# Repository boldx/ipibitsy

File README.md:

# IPIbitsy

[ēpˈbit-sē] \
Stuff to interface with an IBM 9347 9 track tape drive

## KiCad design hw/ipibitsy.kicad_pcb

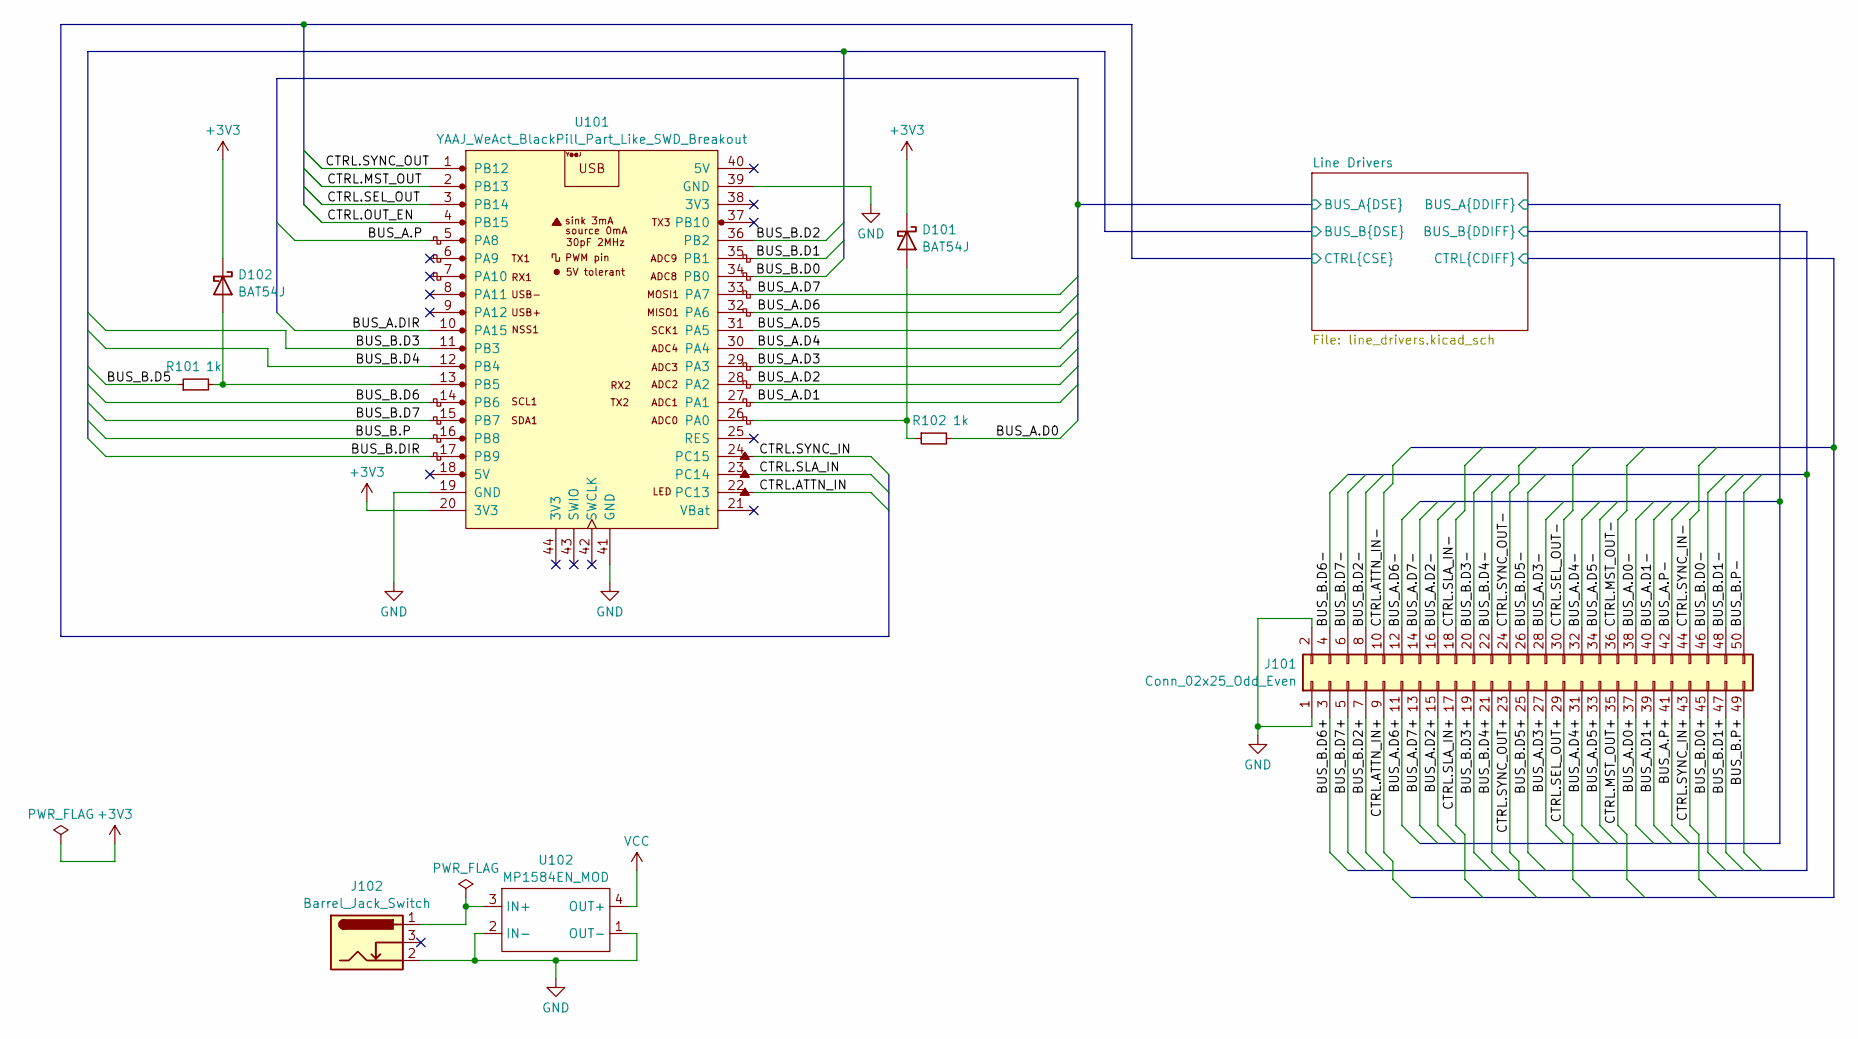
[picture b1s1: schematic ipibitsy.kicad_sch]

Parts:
D101, D102: BAT54J; D_SOD-323_HandSoldering
J101: Conn_02x25_Odd_Even; IDC-Header_2x25_P2.54mm_Vertical
J102: Barrel_Jack_Switch; BarrelJack_Horizontal
R101, R102: 1k; R_0603_1608Metric_Pad0.98x0.95mm_HandSolder
U101: YAAJ_WeAct_BlackPill_Part_Like_SWD_Breakout; YAAJ_WeAct_BlackPill_SWD_2
U102: MP1584EN_MOD

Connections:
+3V3: D101.1 (K), D102.1 (K), U101.20 (3V3)
/Line Drivers/BUS_A.D0: R102.2; also elsewhere on the board
/Line Drivers/BUS_A.D0+: J101.37; also elsewhere on the board
/Line Drivers/BUS_A.D0-: J101.38; also elsewhere on the board
/Line Drivers/BUS_A.D1: U101.27 (PA1); also elsewhere on the board
/Line Drivers/BUS_A.D1+: J101.39; also elsewhere on the board
/Line Drivers/BUS_A.D1-: J101.40; also elsewhere on the board
/Line Drivers/BUS_A.D2: U101.28 (PA2); also elsewhere on the board
/Line Drivers/BUS_A.D2+: J101.15; also elsewhere on the board
/Line Drivers/BUS_A.D2-: J101.16; also elsewhere on the board
/Line Drivers/BUS_A.D3: U101.29 (PA3); also elsewhere on the board
/Line Drivers/BUS_A.D3+: J101.27; also elsewhere on the board
/Line Drivers/BUS_A.D3-: J101.28; also elsewhere on the board
/Line Drivers/BUS_A.D4: U101.30 (PA4); also elsewhere on the board
/Line Drivers/BUS_A.D4+: J101.31; also elsewhere on the board
/Line Drivers/BUS_A.D4-: J101.32; also elsewhere on the board
/Line Drivers/BUS_A.D5: U101.31 (PA5); also elsewhere on the board
/Line Drivers/BUS_A.D5+: J101.33; also elsewhere on the board
/Line Drivers/BUS_A.D5-: J101.34; also elsewhere on the board
/Line Drivers/BUS_A.D6: U101.32 (PA6); also elsewhere on the board
/Line Drivers/BUS_A.D6+: J101.11; also elsewhere on the board
/Line Drivers/BUS_A.D6-: J101.12; also elsewhere on the board
/Line Drivers/BUS_A.D7: U101.33 (PA7); also elsewhere on the board
/Line Drivers/BUS_A.D7+: J101.13; also elsewhere on the board
/Line Drivers/BUS_A.D7-: J101.14; also elsewhere on the board
/Line Drivers/BUS_A.DIR: U101.10 (PA15); also elsewhere on the board
/Line Drivers/BUS_A.P: U101.5 (PA8); also elsewhere on the board
/Line Drivers/BUS_A.P+: J101.41; also elsewhere on the board
/Line Drivers/BUS_A.P-: J101.42; also elsewhere on the board
/Line Drivers/BUS_B.D0: U101.34 (PB0); also elsewhere on the board
/Line Drivers/BUS_B.D0+: J101.45; also elsewhere on the board
/Line Drivers/BUS_B.D0-: J101.46; also elsewhere on the board
/Line Drivers/BUS_B.D1: U101.35 (PB1); also elsewhere on the board
/Line Drivers/BUS_B.D1+: J101.47; also elsewhere on the board
/Line Drivers/BUS_B.D1-: J101.48; also elsewhere on the board
/Line Drivers/BUS_B.D2: U101.36 (PB2); also elsewhere on the board
/Line Drivers/BUS_B.D2+: J101.7; also elsewhere on the board
/Line Drivers/BUS_B.D2-: J101.8; also elsewhere on the board
/Line Drivers/BUS_B.D3: U101.11 (PB3); also elsewhere on the board
/Line Drivers/BUS_B.D3+: J101.19; also elsewhere on the board
/Line Drivers/BUS_B.D3-: J101.20; also elsewhere on the board
/Line Drivers/BUS_B.D4: U101.12 (PB4); also elsewhere on the board
/Line Drivers/BUS_B.D4+: J101.21; also elsewhere on the board
/Line Drivers/BUS_B.D4-: J101.22; also elsewhere on the board
/Line Drivers/BUS_B.D5: R101.1; also elsewhere on the board
/Line Drivers/BUS_B.D5+: J101.25; also elsewhere on the board
/Line Drivers/BUS_B.D5-: J101.26; also elsewhere on the board
/Line Drivers/BUS_B.D6: U101.14 (PB6); also elsewhere on the board
/Line Drivers/BUS_B.D6+: J101.3; also elsewhere on the board
/Line Drivers/BUS_B.D6-: J101.4; also elsewhere on the board
/Line Drivers/BUS_B.D7: U101.15 (PB7); also elsewhere on the board
/Line Drivers/BUS_B.D7+: J101.5; also elsewhere on the board
/Line Drivers/BUS_B.D7-: J101.6; also elsewhere on the board
/Line Drivers/BUS_B.DIR: U101.17 (PB9); also elsewhere on the board
/Line Drivers/BUS_B.P: U101.16 (PB8); also elsewhere on the board
/Line Drivers/BUS_B.P+: J101.49; also elsewhere on the board
/Line Drivers/BUS_B.P-: J101.50; also elsewhere on the board
/Line Drivers/CTRL.ATTN_IN: U101.22 (PC13); also elsewhere on the board
/Line Drivers/CTRL.ATTN_IN+: J101.9; also elsewhere on the board
/Line Drivers/CTRL.ATTN_IN-: J101.10; also elsewhere on the board
/Line Drivers/CTRL.MST_OUT: U101.2 (PB13); also elsewhere on the board
/Line Drivers/CTRL.MST_OUT+: J101.35; also elsewhere on the board
/Line Drivers/CTRL.MST_OUT-: J101.36; also elsewhere on the board
/Line Drivers/CTRL.OUT_EN: U101.4 (PB15); also elsewhere on the board
/Line Drivers/CTRL.SEL_OUT: U101.3 (PB14); also elsewhere on the board
/Line Drivers/CTRL.SEL_OUT+: J101.29; also elsewhere on the board
/Line Drivers/CTRL.SEL_OUT-: J101.30; also elsewhere on the board
/Line Drivers/CTRL.SLA_IN: U101.23 (PC14); also elsewhere on the board
/Line Drivers/CTRL.SLA_IN+: J101.17; also elsewhere on the board
/Line Drivers/CTRL.SLA_IN-: J101.18; also elsewhere on the board
/Line Drivers/CTRL.SYNC_IN: U101.24 (PC15); also elsewhere on the board
/Line Drivers/CTRL.SYNC_IN+: J101.43; also elsewhere on the board
/Line Drivers/CTRL.SYNC_IN-: J101.44; also elsewhere on the board
/Line Drivers/CTRL.SYNC_OUT: U101.1 (PB12); also elsewhere on the board
/Line Drivers/CTRL.SYNC_OUT+: J101.23; also elsewhere on the board
/Line Drivers/CTRL.SYNC_OUT-: J101.24; also elsewhere on the board
unnamed: D101.2 (A), R102.1, U101.26 (PA0)
unnamed: D102.2 (A), R101.2, U101.13 (PB5)
unnamed: J102.1, U102.3 (IN+)

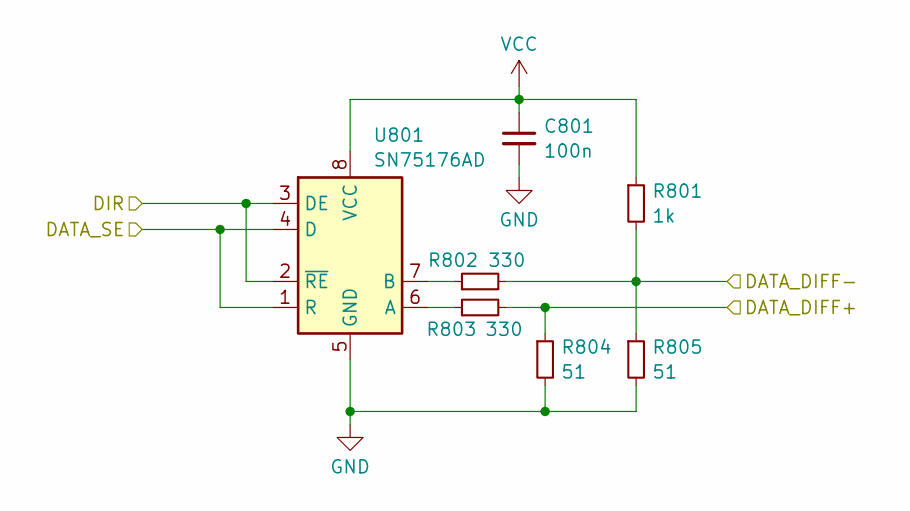
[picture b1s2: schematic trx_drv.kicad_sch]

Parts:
C801: 100n; C_0603_1608Metric_Pad1.08x0.95mm_HandSolder
R801: 1k; R_0603_1608Metric_Pad0.98x0.95mm_HandSolder
R802, R803: 330; R_0603_1608Metric_Pad0.98x0.95mm_HandSolder
R804, R805: 51; R_0603_1608Metric_Pad0.98x0.95mm_HandSolder
U801: SN75176AD; SOIC-8_3.9x4.9mm_P1.27mm

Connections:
/Line Drivers/BUS_A.D5: U801.1 (R), U801.4 (D); also elsewhere on the board
/Line Drivers/BUS_A.D5+: R803.2, R804.1; also elsewhere on the board
/Line Drivers/BUS_A.D5-: R801.2, R802.2, R805.1; also elsewhere on the board
/Line Drivers/BUS_A.DIR: U801.2 (~RE), U801.3 (DE); also elsewhere on the board
unnamed: R803.1, U801.6 (A)
unnamed: R802.1, U801.7 (B)

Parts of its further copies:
C301, C401, C501, C601, C701, C901, C1001, C1101, C1201, C1301, C1401, C1501, C1601, C1701, C1801, C1901, C2001, C2101, C2201, C2301, C2401, C2501, C2601: 100n; C_0603_1608Metric_Pad1.08x0.95mm_HandSolder
R301, R401, R501, R601, R701, R901, R1001, R1101, R1201, R1301, R1401, R1501, R1601, R1701, R1801, R1901, R2001, R2101, R2201, R2301, R2401, R2501, R2601: 1k; R_0603_1608Metric_Pad0.98x0.95mm_HandSolder
R302, R303, R402, R403, R502, R503, R602, R603, R702, R703, R902, R903, R1002, R1003, R1102, R1103, R1202, R1203, R1302, R1303, R1402, R1403, R1502, R1503, R1602, R1603, R1702, R1703, R1802, R1803, R1902, R1903, R2002, R2003, R2102, R2103, R2202, R2203, R2302, R2303, R2402, R2403, R2502, R2503, R2602, R2603: 330; R_0603_1608Metric_Pad0.98x0.95mm_HandSolder
R304, R305, R404, R405, R504, R505, R604, R605, R704, R705, R904, R905, R1004, R1005, R1104, R1105, R1204, R1205, R1304, R1305, R1404, R1405, R1504, R1505, R1604, R1605, R1704, R1705, R1804, R1805, R1904, R1905, R2004, R2005, R2104, R2105, R2204, R2205, R2304, R2305, R2404, R2405, R2504, R2505, R2604, R2605: 51; R_0603_1608Metric_Pad0.98x0.95mm_HandSolder
U301, U401, U501, U601, U701, U901, U1001, U1101, U1201, U1301, U1401, U1501, U1601, U1701, U1801, U1901, U2001, U2101, U2201, U2301, U2401, U2501, U2601: SN75176AD; SOIC-8_3.9x4.9mm_P1.27mm

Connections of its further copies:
/Line Drivers/BUS_A.D0: U301.1 (R), U301.4 (D); also elsewhere on the board
/Line Drivers/BUS_A.D0+: R303.2, R304.1; also elsewhere on the board
/Line Drivers/BUS_A.D0-: R301.2, R302.2, R305.1; also elsewhere on the board
/Line Drivers/BUS_A.D1: U401.1 (R), U401.4 (D); also elsewhere on the board
/Line Drivers/BUS_A.D1+: R403.2, R404.1; also elsewhere on the board
/Line Drivers/BUS_A.D1-: R401.2, R402.2, R405.1; also elsewhere on the board
/Line Drivers/BUS_A.D2: U501.1 (R), U501.4 (D); also elsewhere on the board
/Line Drivers/BUS_A.D2+: R503.2, R504.1; also elsewhere on the board
/Line Drivers/BUS_A.D2-: R501.2, R502.2, R505.1; also elsewhere on the board
/Line Drivers/BUS_A.D3: U601.1 (R), U601.4 (D); also elsewhere on the board
/Line Drivers/BUS_A.D3+: R603.2, R604.1; also elsewhere on the board
/Line Drivers/BUS_A.D3-: R601.2, R602.2, R605.1; also elsewhere on the board
/Line Drivers/BUS_A.D4: U701.1 (R), U701.4 (D); also elsewhere on the board
/Line Drivers/BUS_A.D4+: R703.2, R704.1; also elsewhere on the board
/Line Drivers/BUS_A.D4-: R701.2, R702.2, R705.1; also elsewhere on the board
/Line Drivers/BUS_A.D6: U901.1 (R), U901.4 (D); also elsewhere on the board
/Line Drivers/BUS_A.D6+: R903.2, R904.1; also elsewhere on the board
/Line Drivers/BUS_A.D6-: R901.2, R902.2, R905.1; also elsewhere on the board
/Line Drivers/BUS_A.D7: U1001.1 (R), U1001.4 (D); also elsewhere on the board
/Line Drivers/BUS_A.D7+: R1003.2, R1004.1; also elsewhere on the board
/Line Drivers/BUS_A.D7-: R1001.2, R1002.2, R1005.1; also elsewhere on the board
/Line Drivers/BUS_A.DIR: U301.2 (~RE), U301.3 (DE), U401.2 (~RE), U401.3 (DE), U501.2 (~RE), U501.3 (DE), U601.2 (~RE), U601.3 (DE), U701.2 (~RE), U701.3 (DE), U901.2 (~RE), U901.3 (DE), U1001.2 (~RE), U1001.3 (DE), U1101.2 (~RE), U1101.3 (DE); also elsewhere on the board
/Line Drivers/BUS_A.P: U1101.1 (R), U1101.4 (D); also elsewhere on the board
/Line Drivers/BUS_A.P+: R1103.2, R1104.1; also elsewhere on the board
/Line Drivers/BUS_A.P-: R1101.2, R1102.2, R1105.1; also elsewhere on the board
/Line Drivers/BUS_B.D0: U1201.1 (R), U1201.4 (D); also elsewhere on the board
/Line Drivers/BUS_B.D0+: R1203.2, R1204.1; also elsewhere on the board
/Line Drivers/BUS_B.D0-: R1201.2, R1202.2, R1205.1; also elsewhere on the board
/Line Drivers/BUS_B.D1: U1301.1 (R), U1301.4 (D); also elsewhere on the board
/Line Drivers/BUS_B.D1+: R1303.2, R1304.1; also elsewhere on the board
/Line Drivers/BUS_B.D1-: R1301.2, R1302.2, R1305.1; also elsewhere on the board
/Line Drivers/BUS_B.D2: U1401.1 (R), U1401.4 (D); also elsewhere on the board
/Line Drivers/BUS_B.D2+: R1403.2, R1404.1; also elsewhere on the board
/Line Drivers/BUS_B.D2-: R1401.2, R1402.2, R1405.1; also elsewhere on the board
/Line Drivers/BUS_B.D3: U1501.1 (R), U1501.4 (D); also elsewhere on the board
/Line Drivers/BUS_B.D3+: R1503.2, R1504.1; also elsewhere on the board
/Line Drivers/BUS_B.D3-: R1501.2, R1502.2, R1505.1; also elsewhere on the board
/Line Drivers/BUS_B.D4: U1601.1 (R), U1601.4 (D); also elsewhere on the board
/Line Drivers/BUS_B.D4+: R1603.2, R1604.1; also elsewhere on the board
/Line Drivers/BUS_B.D4-: R1601.2, R1602.2, R1605.1; also elsewhere on the board
/Line Drivers/BUS_B.D5: U1701.1 (R), U1701.4 (D); also elsewhere on the board
/Line Drivers/BUS_B.D5+: R1703.2, R1704.1; also elsewhere on the board
/Line Drivers/BUS_B.D5-: R1701.2, R1702.2, R1705.1; also elsewhere on the board
/Line Drivers/BUS_B.D6: U1801.1 (R), U1801.4 (D); also elsewhere on the board
/Line Drivers/BUS_B.D6+: R1803.2, R1804.1; also elsewhere on the board
/Line Drivers/BUS_B.D6-: R1801.2, R1802.2, R1805.1; also elsewhere on the board
/Line Drivers/BUS_B.D7: U1901.1 (R), U1901.4 (D); also elsewhere on the board
/Line Drivers/BUS_B.D7+: R1903.2, R1904.1; also elsewhere on the board
/Line Drivers/BUS_B.D7-: R1901.2, R1902.2, R1905.1; also elsewhere on the board
/Line Drivers/BUS_B.DIR: U1201.2 (~RE), U1201.3 (DE), U1301.2 (~RE), U1301.3 (DE), U1401.2 (~RE), U1401.3 (DE), U1501.2 (~RE), U1501.3 (DE), U1601.2 (~RE), U1601.3 (DE), U1701.2 (~RE), U1701.3 (DE), U1801.2 (~RE), U1801.3 (DE), U1901.2 (~RE), U1901.3 (DE), U2001.2 (~RE), U2001.3 (DE); also elsewhere on the board
/Line Drivers/BUS_B.P: U2001.1 (R), U2001.4 (D); also elsewhere on the board
/Line Drivers/BUS_B.P+: R2003.2, R2004.1; also elsewhere on the board
/Line Drivers/BUS_B.P-: R2001.2, R2002.2, R2005.1; also elsewhere on the board
/Line Drivers/CTRL.ATTN_IN: U2301.1 (R); also elsewhere on the board
/Line Drivers/CTRL.ATTN_IN+: R2303.2, R2304.1; also elsewhere on the board
/Line Drivers/CTRL.ATTN_IN-: R2301.2, R2302.2, R2305.1; also elsewhere on the board
/Line Drivers/CTRL.MST_OUT: U2501.4 (D); also elsewhere on the board
/Line Drivers/CTRL.MST_OUT+: R2503.2, R2504.1; also elsewhere on the board
/Line Drivers/CTRL.MST_OUT-: R2501.2, R2502.2, R2505.1; also elsewhere on the board
/Line Drivers/CTRL.OUT_EN: U2401.3 (DE), U2501.3 (DE), U2601.3 (DE); also elsewhere on the board
/Line Drivers/CTRL.SEL_OUT: U2601.4 (D); also elsewhere on the board
/Line Drivers/CTRL.SEL_OUT+: R2603.2, R2604.1; also elsewhere on the board
/Line Drivers/CTRL.SEL_OUT-: R2601.2, R2602.2, R2605.1; also elsewhere on the board
/Line Drivers/CTRL.SLA_IN: U2201.1 (R); also elsewhere on the board
/Line Drivers/CTRL.SLA_IN+: R2203.2, R2204.1; also elsewhere on the board
/Line Drivers/CTRL.SLA_IN-: R2201.2, R2202.2, R2205.1; also elsewhere on the board
/Line Drivers/CTRL.SYNC_IN: U2101.1 (R); also elsewhere on the board
/Line Drivers/CTRL.SYNC_IN+: R2103.2, R2104.1; also elsewhere on the board
/Line Drivers/CTRL.SYNC_IN-: R2101.2, R2102.2, R2105.1; also elsewhere on the board
/Line Drivers/CTRL.SYNC_OUT: U2401.4 (D); also elsewhere on the board
/Line Drivers/CTRL.SYNC_OUT+: R2403.2, R2404.1; also elsewhere on the board
/Line Drivers/CTRL.SYNC_OUT-: R2401.2, R2402.2, R2405.1; also elsewhere on the board
unnamed: R303.1, U301.6 (A)
unnamed: R302.1, U301.7 (B)
unnamed: R403.1, U401.6 (A)
unnamed: R402.1, U401.7 (B)
unnamed: R503.1, U501.6 (A)
unnamed: R502.1, U501.7 (B)
unnamed: R603.1, U601.6 (A)
unnamed: R602.1, U601.7 (B)
unnamed: R703.1, U701.6 (A)
unnamed: R702.1, U701.7 (B)
unnamed: R903.1, U901.6 (A)
unnamed: R902.1, U901.7 (B)
unnamed: R1003.1, U1001.6 (A)
unnamed: R1002.1, U1001.7 (B)
unnamed: R1103.1, U1101.6 (A)
unnamed: R1102.1, U1101.7 (B)
unnamed: R1203.1, U1201.6 (A)
unnamed: R1202.1, U1201.7 (B)
unnamed: R1303.1, U1301.6 (A)
unnamed: R1302.1, U1301.7 (B)
unnamed: R1403.1, U1401.6 (A)
unnamed: R1402.1, U1401.7 (B)
unnamed: R1503.1, U1501.6 (A)
unnamed: R1502.1, U1501.7 (B)
unnamed: R1603.1, U1601.6 (A)
unnamed: R1602.1, U1601.7 (B)
unnamed: R1703.1, U1701.6 (A)
unnamed: R1702.1, U1701.7 (B)
unnamed: R1803.1, U1801.6 (A)
unnamed: R1802.1, U1801.7 (B)
unnamed: R1903.1, U1901.6 (A)
unnamed: R1902.1, U1901.7 (B)
unnamed: R2003.1, U2001.6 (A)
unnamed: R2002.1, U2001.7 (B)
unnamed: R2103.1, U2101.6 (A)
unnamed: R2102.1, U2101.7 (B)
unnamed: R2203.1, U2201.6 (A)
unnamed: R2202.1, U2201.7 (B)
unnamed: R2303.1, U2301.6 (A)
unnamed: R2302.1, U2301.7 (B)
unnamed: R2403.1, U2401.6 (A)
unnamed: R2402.1, U2401.7 (B)
unnamed: R2503.1, U2501.6 (A)
unnamed: R2502.1, U2501.7 (B)
unnamed: R2603.1, U2601.6 (A)
unnamed: R2602.1, U2601.7 (B)

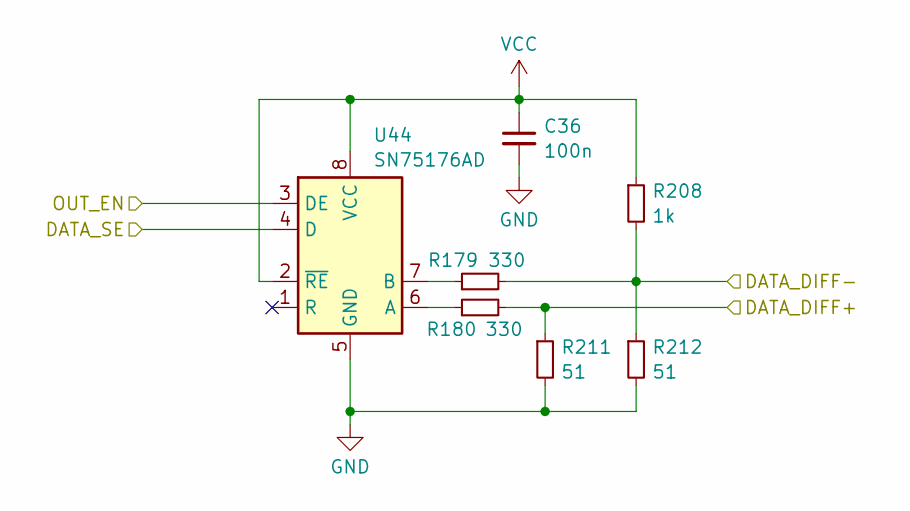
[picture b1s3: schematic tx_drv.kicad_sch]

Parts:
C36: 100n; C_0603_1608Metric_Pad1.08x0.95mm_HandSolder
R179, R180: 330; R_0603_1608Metric_Pad0.98x0.95mm_HandSolder
R208: 1k; R_0603_1608Metric_Pad0.98x0.95mm_HandSolder
R211, R212: 51; R_0603_1608Metric_Pad0.98x0.95mm_HandSolder
U44: SN75176AD; SOIC-8_3.9x4.9mm_P1.27mm

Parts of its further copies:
C2101, C2401, C2501, C2601: 100n; C_0603_1608Metric_Pad1.08x0.95mm_HandSolder
R2101, R2401, R2501, R2601: 1k; R_0603_1608Metric_Pad0.98x0.95mm_HandSolder
R2102, R2103, R2402, R2403, R2502, R2503, R2602, R2603: 330; R_0603_1608Metric_Pad0.98x0.95mm_HandSolder
R2104, R2105, R2404, R2405, R2504, R2505, R2604, R2605: 51; R_0603_1608Metric_Pad0.98x0.95mm_HandSolder
U2101, U2401, U2501, U2601: SN75176AD; SOIC-8_3.9x4.9mm_P1.27mm

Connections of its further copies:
/Line Drivers/CTRL.MST_OUT: U2501.4 (D); also elsewhere on the board
/Line Drivers/CTRL.MST_OUT+: R2503.2, R2504.1; also elsewhere on the board
/Line Drivers/CTRL.MST_OUT-: R2501.2, R2502.2, R2505.1; also elsewhere on the board
/Line Drivers/CTRL.OUT_EN: U2401.3 (DE), U2501.3 (DE), U2601.3 (DE); also elsewhere on the board
/Line Drivers/CTRL.SEL_OUT: U2601.4 (D); also elsewhere on the board
/Line Drivers/CTRL.SEL_OUT+: R2603.2, R2604.1; also elsewhere on the board
/Line Drivers/CTRL.SEL_OUT-: R2601.2, R2602.2, R2605.1; also elsewhere on the board
/Line Drivers/CTRL.SYNC_IN: U2101.1 (R); also elsewhere on the board
/Line Drivers/CTRL.SYNC_IN+: R2103.2, R2104.1; also elsewhere on the board
/Line Drivers/CTRL.SYNC_IN-: R2101.2, R2102.2, R2105.1; also elsewhere on the board
/Line Drivers/CTRL.SYNC_OUT: U2401.4 (D); also elsewhere on the board
/Line Drivers/CTRL.SYNC_OUT+: R2403.2, R2404.1; also elsewhere on the board
/Line Drivers/CTRL.SYNC_OUT-: R2401.2, R2402.2, R2405.1; also elsewhere on the board
unnamed: R2103.1, U2101.6 (A)
unnamed: R2102.1, U2101.7 (B)
unnamed: R2403.1, U2401.6 (A)
unnamed: R2402.1, U2401.7 (B)
unnamed: R2503.1, U2501.6 (A)
unnamed: R2502.1, U2501.7 (B)
unnamed: R2603.1, U2601.6 (A)
unnamed: R2602.1, U2601.7 (B)

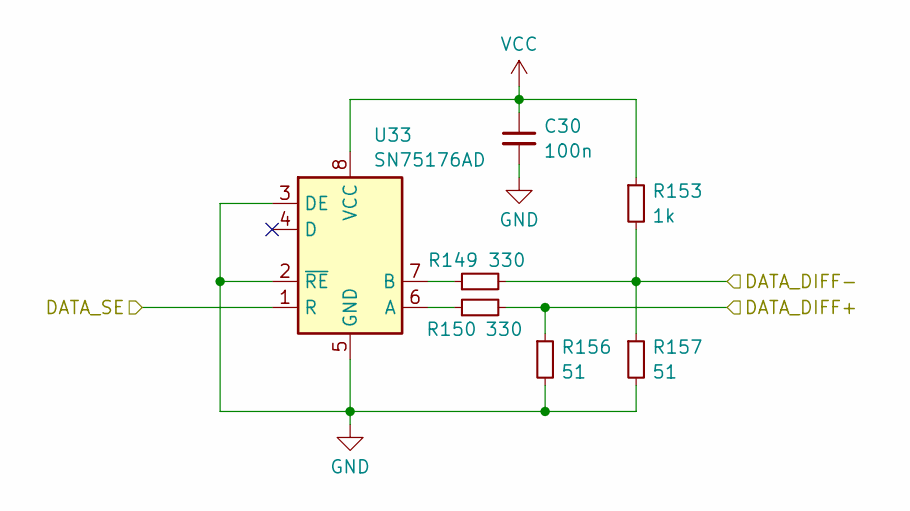
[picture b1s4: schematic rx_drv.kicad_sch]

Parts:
C30: 100n; C_0603_1608Metric_Pad1.08x0.95mm_HandSolder
R149, R150: 330; R_0603_1608Metric_Pad0.98x0.95mm_HandSolder
R153: 1k; R_0603_1608Metric_Pad0.98x0.95mm_HandSolder
R156, R157: 51; R_0603_1608Metric_Pad0.98x0.95mm_HandSolder
U33: SN75176AD; SOIC-8_3.9x4.9mm_P1.27mm

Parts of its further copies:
C2101, C2201, C2301: 100n; C_0603_1608Metric_Pad1.08x0.95mm_HandSolder
R2101, R2201, R2301: 1k; R_0603_1608Metric_Pad0.98x0.95mm_HandSolder
R2102, R2103, R2202, R2203, R2302, R2303: 330; R_0603_1608Metric_Pad0.98x0.95mm_HandSolder
R2104, R2105, R2204, R2205, R2304, R2305: 51; R_0603_1608Metric_Pad0.98x0.95mm_HandSolder
U2101, U2201, U2301: SN75176AD; SOIC-8_3.9x4.9mm_P1.27mm

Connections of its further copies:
/Line Drivers/CTRL.ATTN_IN: U2301.1 (R); also elsewhere on the board
/Line Drivers/CTRL.ATTN_IN+: R2303.2, R2304.1; also elsewhere on the board
/Line Drivers/CTRL.ATTN_IN-: R2301.2, R2302.2, R2305.1; also elsewhere on the board
/Line Drivers/CTRL.SLA_IN: U2201.1 (R); also elsewhere on the board
/Line Drivers/CTRL.SLA_IN+: R2203.2, R2204.1; also elsewhere on the board
/Line Drivers/CTRL.SLA_IN-: R2201.2, R2202.2, R2205.1; also elsewhere on the board
/Line Drivers/CTRL.SYNC_IN: U2101.1 (R); also elsewhere on the board
/Line Drivers/CTRL.SYNC_IN+: R2103.2, R2104.1; also elsewhere on the board
/Line Drivers/CTRL.SYNC_IN-: R2101.2, R2102.2, R2105.1; also elsewhere on the board
unnamed: R2103.1, U2101.6 (A)
unnamed: R2102.1, U2101.7 (B)
unnamed: R2203.1, U2201.6 (A)
unnamed: R2202.1, U2201.7 (B)
unnamed: R2303.1, U2301.6 (A)
unnamed: R2302.1, U2301.7 (B)

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
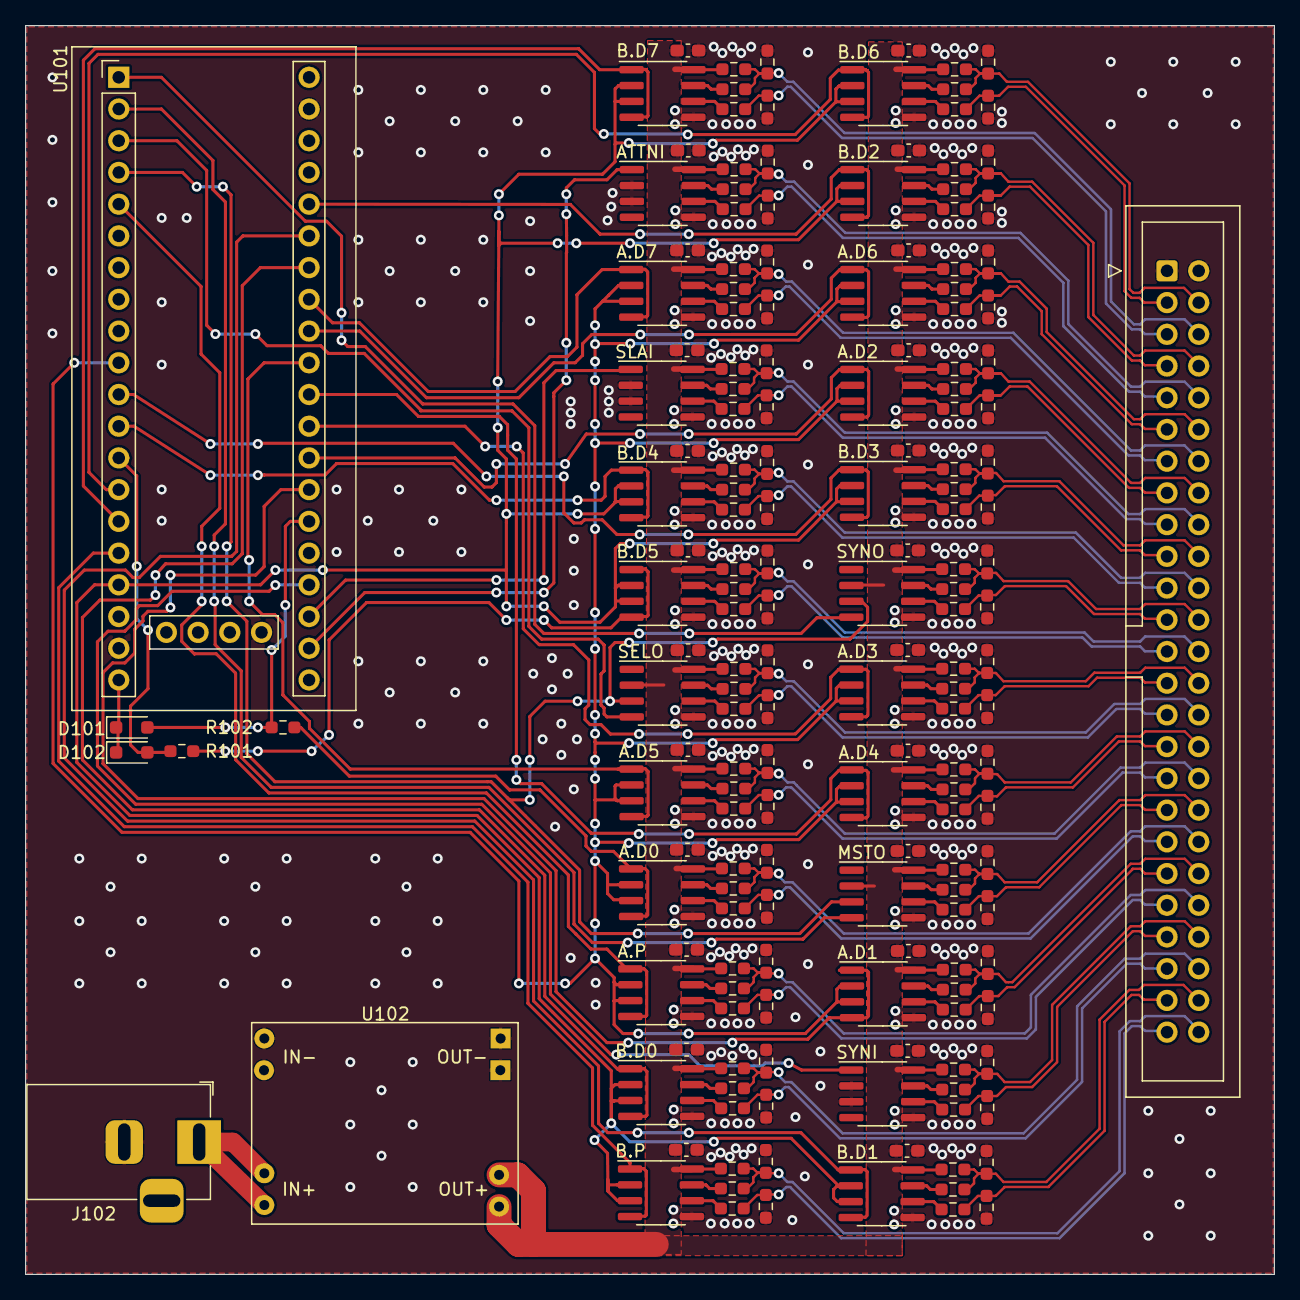
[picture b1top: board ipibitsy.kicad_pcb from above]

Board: 2 copper layers, 100.0 x 100.0 mm, 176 parts (0 on the bottom side), 129 nets.

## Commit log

2023-10-09 First prototype version of the HW
2023-10-09 Readme, gitignore
2023-10-09 pdf export
2023-10-10 oops
2023-10-10 attempt to describe the pronunciation
2023-12-07 BUS*B* Parity bit driver direction pin was accidentally connected to BUS*A* direction net
2025-06-14 Some changes I'm not sure about when and why was made >.<
2025-06-14 Initial firmware
2025-06-14 First attempts to communicate
2025-06-14 Some cleanup
